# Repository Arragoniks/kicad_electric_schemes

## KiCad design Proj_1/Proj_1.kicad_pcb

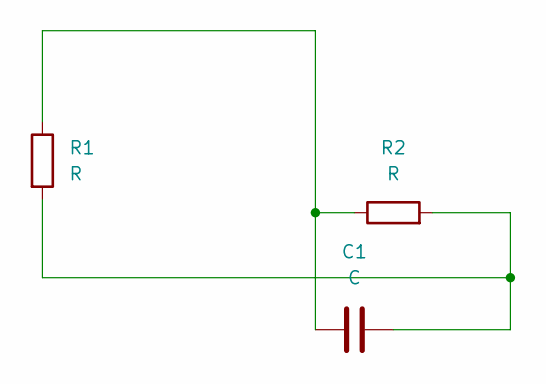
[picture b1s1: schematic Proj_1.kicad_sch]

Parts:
C1: C; CP_Axial_L10.0mm_D6.0mm_P15.00mm_Horizontal
R1, R2: R; R_Axial_DIN0204_L3.6mm_D1.6mm_P7.62mm_Horizontal

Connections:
unnamed: C1.1, R1.1, R2.1
unnamed: C1.2, R1.2, R2.2

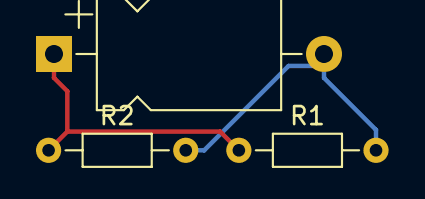
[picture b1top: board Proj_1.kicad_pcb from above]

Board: 2 copper layers, 3 parts (0 on the bottom side), 2 nets.

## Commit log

2023-04-22 Add few passive elements to increase stability. Changed schematic size from A4 to A3.
2023-04-23 Add some theory.
